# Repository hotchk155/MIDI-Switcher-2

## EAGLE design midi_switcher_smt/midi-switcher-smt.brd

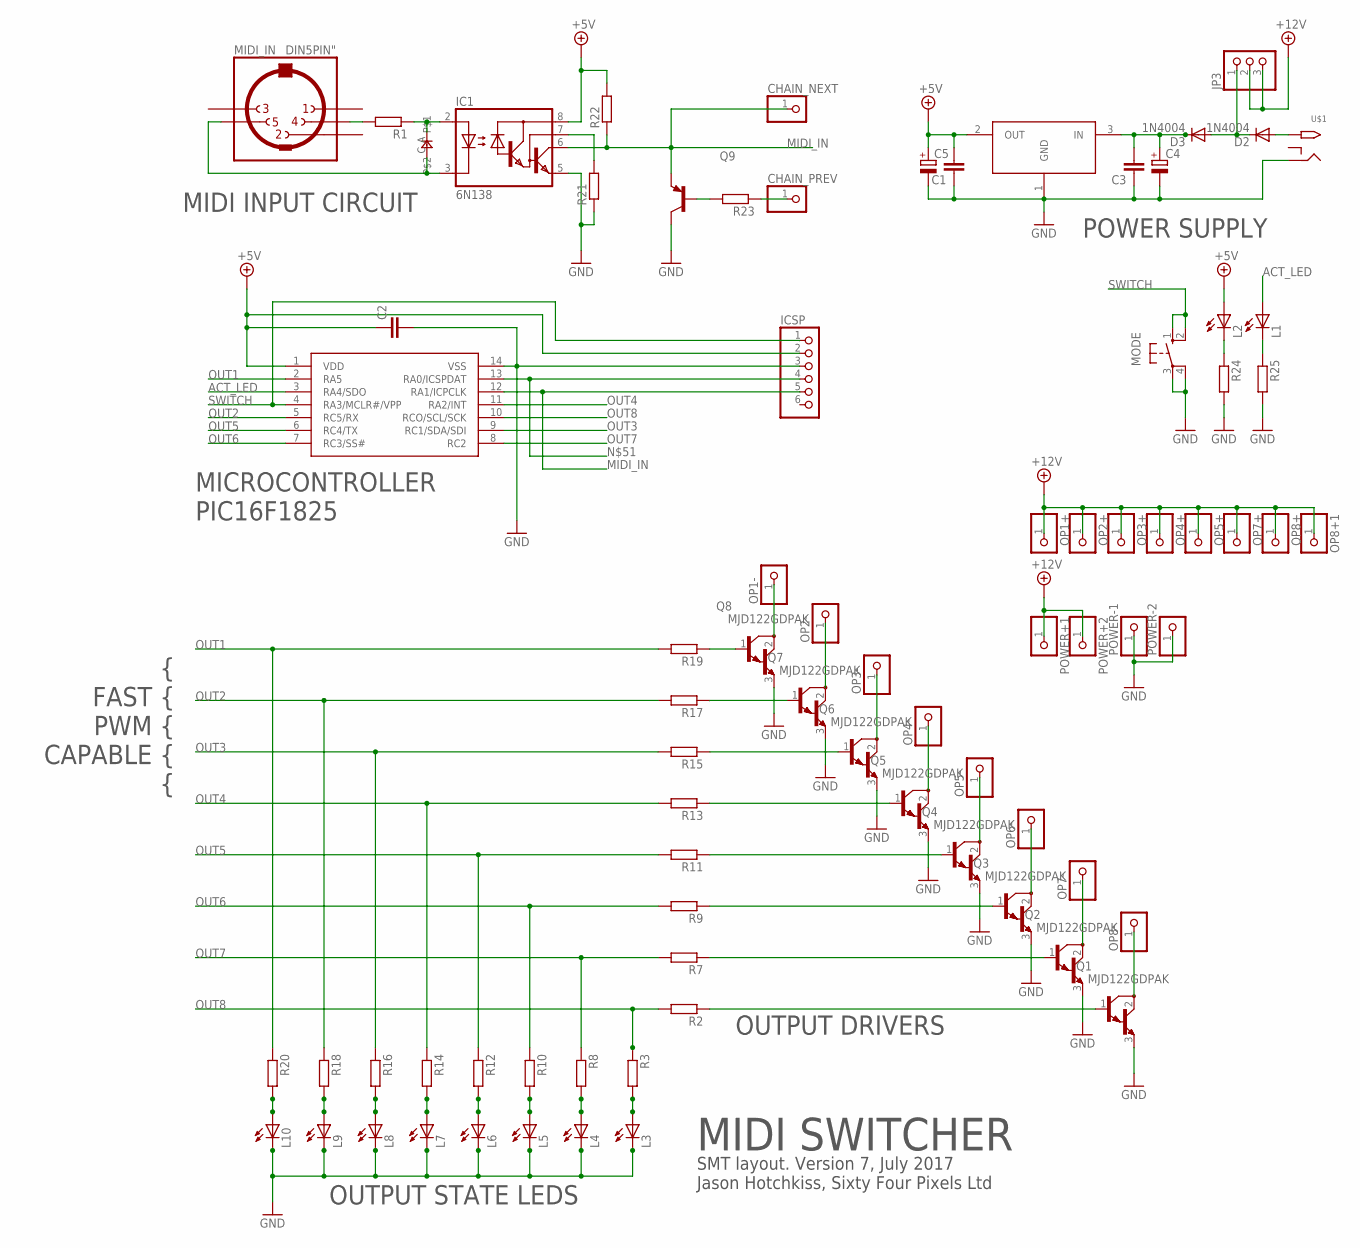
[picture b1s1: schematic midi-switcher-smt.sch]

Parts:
C1, C2, C3: C-EUC0805; C0805
C4: CPOL-EUE2.5-7; E2,5-7
C5: CPOL-EUE2.5-6; E2,5-6
CHAIN_NEXT: PINHD-1X1; 1X01
CHAIN_PREV: PINHD-1X1; 1X01
D1: 0805DIODE
D2, D3: 1N4004; DO-VERT
IC1: 6N138; DIL08
IC2: PIC16F1825SO14; SO14
IC3: LD1086; DPACK
ICSP: HEADER-1X6; 1X06_OVAL
JP3: PINHD-1X3; 1X03
L1, L2, L3, L4, L5, L6, L7, L8, L9, L10: LEDCHIP-LED0805; CHIP-LED0805
MIDI_IN: DIN5PIN"; TRUCONN90
MODE: 10-XX; B3F-10XX
OP1+, OP1-, OP2+, OP2-, OP3+, OP3-, OP4+, OP4-, OP5+, OP5-, OP6-, OP7+, OP7-, OP8+, OP8+1, OP8-: PINHD-1X1; 1X01W
POWER+1, POWER+2: PINHD-1X1; 1X01W
POWER-1, POWER-2: PINHD-1X1; 1X01W
Q1, Q2, Q3, Q4, Q5, Q6, Q7, Q8: MJD122GDPAK; DPACK
Q9: MMBT3906LT1-PNP-SOT23-BEC; SOT23-BEC
R1, R2, R3, R7, R8, R9, R10, R11, R12, R13, R14, R15, R16, R17, R18, R19, R20, R21, R22, R23, R24, R25: R-EU_R0805; R0805
U$1: 2.1MMJACKTHM; PJ-102A

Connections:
+5V: C1.2, C2.1, C5.+, IC1.8 (VCC), IC2.1 (VDD), IC3.2 (OUT), ICSP.2, L2.A, R22.2
+12V: JP3.2, JP3.3, OP1+.1, OP2+.1, OP3+.1, OP4+.1, OP5+.1, OP7+.1, OP8+.1, OP8+1.1, POWER+1.1, POWER+2.1
ACT_LED: IC2.3 (RA4/SDO), L1.A
GND: C1.1, C2.2, C3.1, C4.-, C5.-, IC1.5 (GND), IC2.14 (VSS), IC3.1 (GND), ICSP.3, L3.C, L4.C, L5.C, L6.C, L7.C, L8.C, L9.C, L10.C, MODE.3, MODE.4 (P1), POWER-1.1, POWER-2.1, Q1.3 (E), Q2.3 (E), Q3.3 (E), Q4.3 (E), Q5.3 (E), Q6.3 (E), Q7.3 (E), Q8.3 (E), Q9.C, R21.1, R24.2, R25.2, U$1.RING
MIDI_IN: CHAIN_NEXT.1, IC1.6 (VO), IC2.12 (RA1/ICPCLK), ICSP.5, Q9.E, R22.1
unnamed: D1.C, IC1.3 (C), MIDI_IN.5
unnamed: MIDI_IN.4, R1.2
unnamed: D1.A, IC1.2 (A), R1.1
unnamed: IC1.7 (VB), R21.2
unnamed: L1.C, R25.1
unnamed: L10.A, R20.2
unnamed: L9.A, R18.2
unnamed: Q8.1 (B), R19.1
unnamed: Q7.1 (B), R17.1
unnamed: Q6.1 (B), R15.1
unnamed: Q5.1 (B), R13.1
unnamed: Q4.1 (B), R11.1
unnamed: Q3.1 (B), R9.1
unnamed: Q2.1 (B), R7.1
unnamed: Q1.1 (B), R2.1
unnamed: Q9.B, R23.2
unnamed: CHAIN_PREV.1, R23.1
unnamed: L8.A, R16.2
unnamed: OP1-.1, Q8.2 (C)
unnamed: OP2-.1, Q7.2 (C)
unnamed: OP3-.1, Q6.2 (C)
unnamed: L2.C, R24.1
unnamed: OP5-.1, Q4.2 (C)
unnamed: OP6-.1, Q3.2 (C)
unnamed: OP4-.1, Q5.2 (C)
unnamed: L7.A, R14.2
unnamed: L6.A, R12.2
unnamed: L5.A, R10.2
unnamed: L4.A, R8.2
unnamed: L3.A, R3.2
unnamed: C3.2, C4.+, D3.C, IC3.3 (IN)
unnamed: OP7-.1, Q2.2 (C)
unnamed: D2.A, U$1.TIP
unnamed: OP8-.1, Q1.2 (C)
unnamed: IC2.13 (RA0/ICSPDAT), ICSP.4
unnamed: D2.C, D3.A, JP3.1
OUT1: IC2.2 (RA5), R19.2, R20.1
OUT2: IC2.5 (RC5/RX), R17.2, R18.1
OUT3: IC2.9 (RC1/SDA/SDI), R15.2, R16.1
OUT4: IC2.11 (RA2/INT), R13.2, R14.1
OUT5: IC2.6 (RC4/TX), R11.2, R12.1
OUT6: IC2.7 (RC3/SS#), R9.2, R10.1
OUT7: IC2.8 (RC2), R7.2, R8.1
OUT8: IC2.10 (RCO/SCL/SCK), R2.2, R3.1
SWITCH: IC2.4 (RA3/MCLR#/VPP), ICSP.1, MODE.1 (S), MODE.2 (S1)

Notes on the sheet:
MIDI SWITCHER
SMT layout. Version 7, July 2017 Jason Hotchkiss, Sixty Four Pixels Ltd
MIDI INPUT CIRCUIT
MICROCONTROLLER PIC16F1825
POWER SUPPLY
OUTPUT STATE LEDS
OUTPUT DRIVERS
{ FAST { PWM { CAPABLE { {

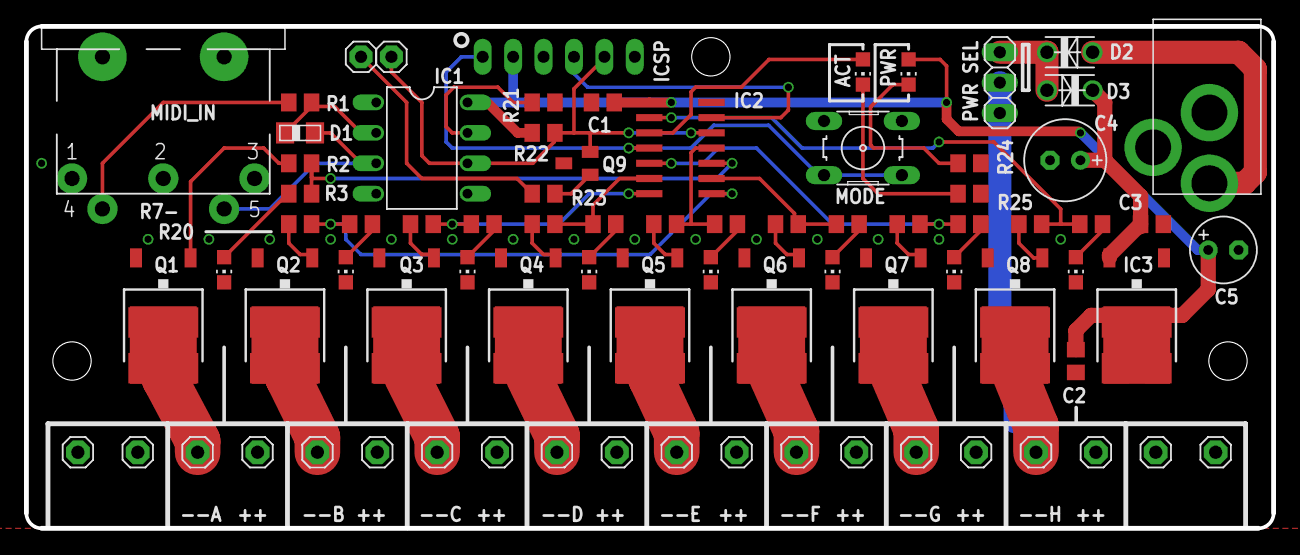
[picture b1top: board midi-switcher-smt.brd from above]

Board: 2 copper layers, 104.1 x 41.9 mm, 79 parts (0 on the bottom side), 50 nets.

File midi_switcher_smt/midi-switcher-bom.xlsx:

Comment | Designator | Footprint | JLCPCB Part #（optional）
100n | C1 | 0805
100n | C2 | 0805
100n | C3 | 0805
TS4148 | D1 | 0805
PIC16F1825-I/SL | IC2 | SOIC-14 | C19649
LD1086DT50TR | IC3 | DPAK | C164853
blue | L1 | 0805
red | L2 | 0805
blue | L3 | 0805
blue | L4 | 0805
blue | L5 | 0805
blue | L6 | 0805
blue | L7 | 0805
blue | L8 | 0805
blue | L9 | 0805
blue | L10 | 0805
MJD122G | Q1 | DPAK | C89910
MJD122G | Q2 | DPAK | C89910
MJD122G | Q3 | DPAK | C89910
MJD122G | Q4 | DPAK | C89910
MJD122G | Q5 | DPAK | C89910
MJD122G | Q6 | DPAK | C89910
MJD122G | Q7 | DPAK | C89910
MJD122G | Q8 | DPAK | C89910
MMBT3906 | Q9 | SOT23-3
220 | R1 | R0805
1k | R2 | R0805
1k | R3 | R0805
1k | R7 | R0805
1k | R8 | R0805
1k | R9 | R0805
1k | R10 | R0805
1k | R11 | R0805
1k | R12 | R0805
1k | R13 | R0805
1k | R14 | R0805
1k | R15 | R0805
1k | R16 | R0805
1k | R17 | R0805
1k | R18 | R0805
1k | R19 | R0805
1k | R20 | R0805
1.5k | R21 | R0805
1.5k | R22 | R0805
1k | R23 | R0805
1k | R24 | R0805
1k | R25 | R0805

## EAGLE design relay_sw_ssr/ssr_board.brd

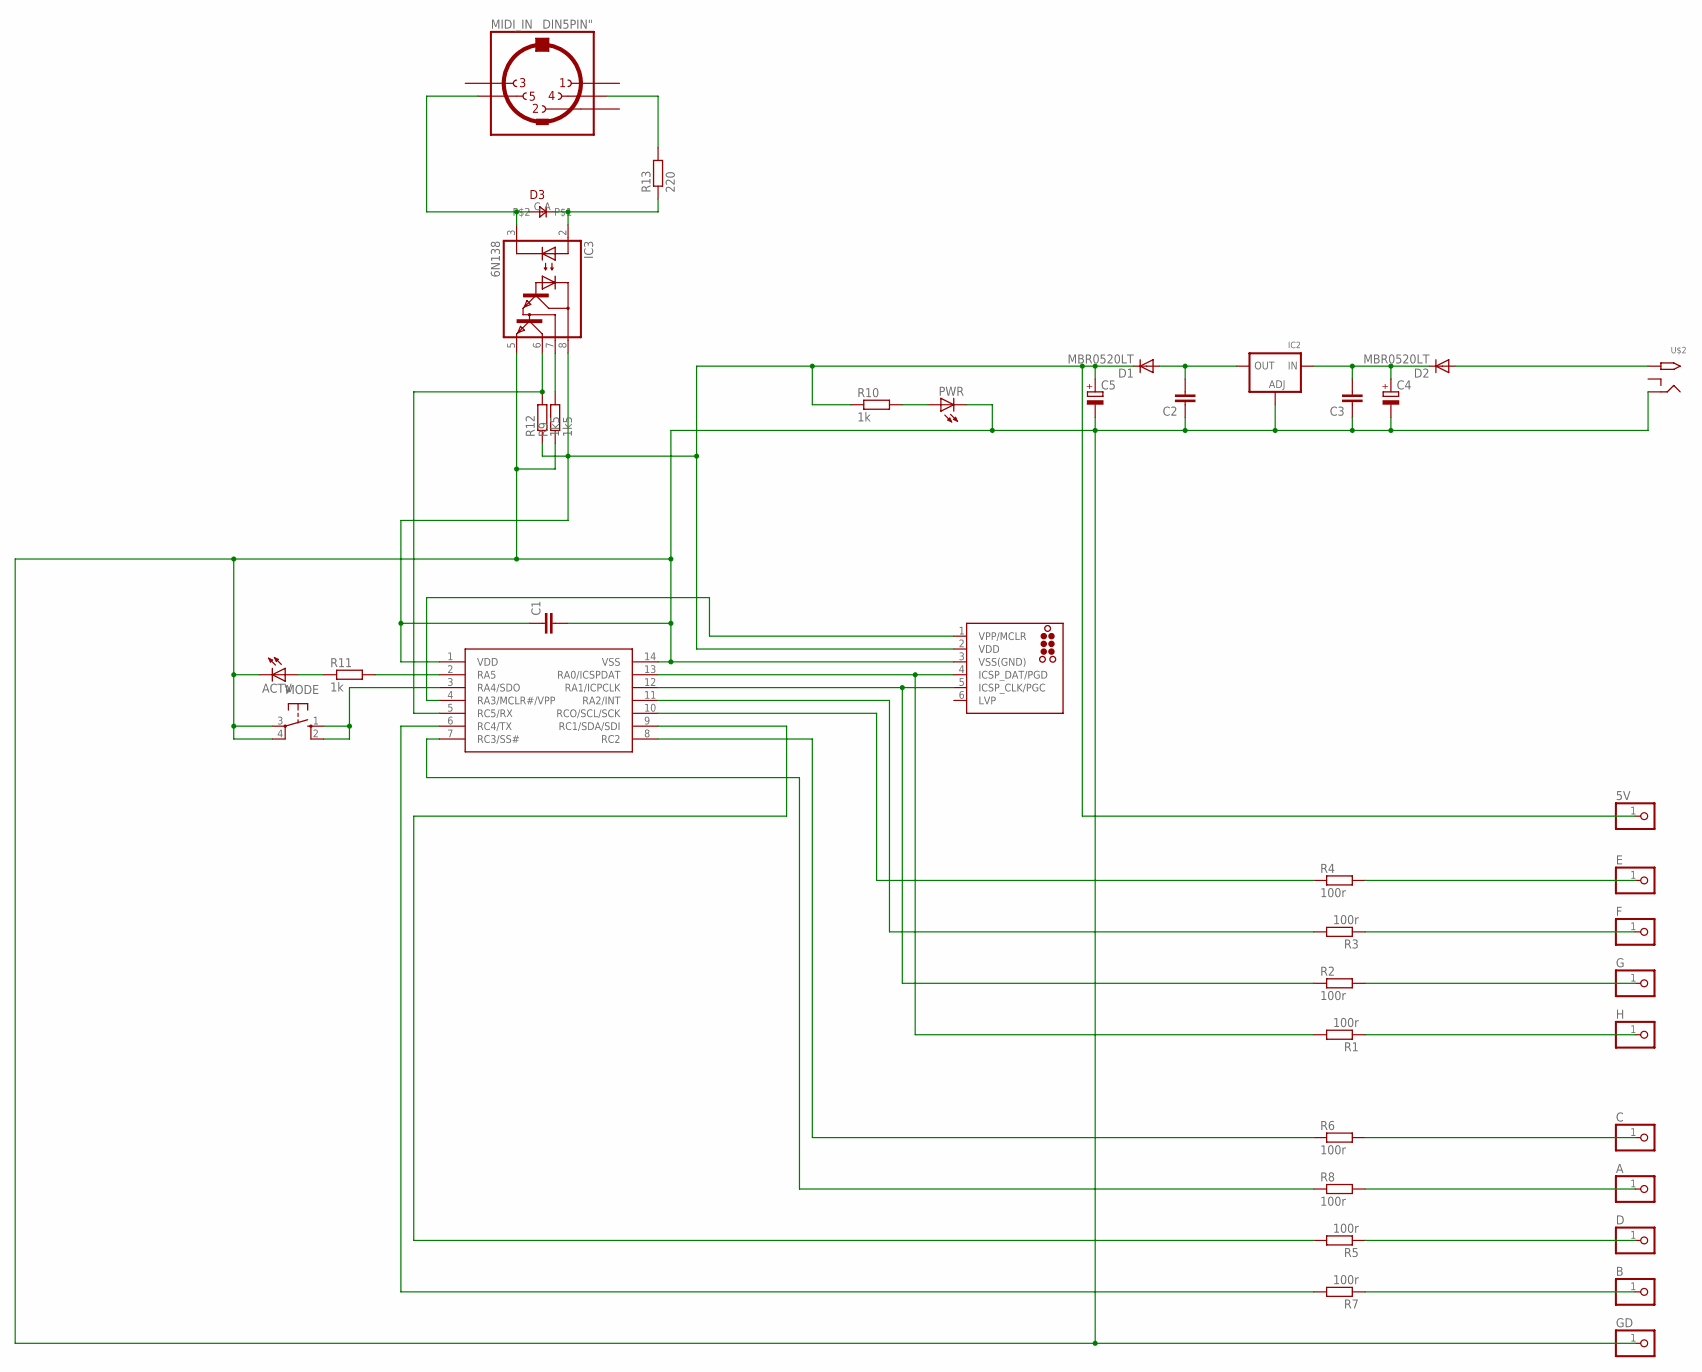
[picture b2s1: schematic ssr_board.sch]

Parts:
5V: PINHD-1X1; 1X01
A: PINHD-1X1; 1X01
ACTV: LED3MM
B: PINHD-1X1; 1X01
C: PINHD-1X1; 1X01
C1, C2, C3: C-EUC0805; C0805
C4, C5: CPOL-EUE2-5; E2-5
D: PINHD-1X1; 1X01
D1, D2: MBR0520LT; SOD123
D3: 0805DIODE
E: PINHD-1X1; 1X01
F: PINHD-1X1; 1X01
G: PINHD-1X1; 1X01
GD: PINHD-1X1; 1X01
H: PINHD-1X1; 1X01
IC1: PIC16F1825SO14; SO14
IC2: LM1117SOT223-WAVE; SOT223-W
IC3: 6N138; DIL08
ICSP: TC2030-MCP-NL
MIDI_IN: DIN5PIN"; TRUCONN90
MODE: 10-XX; B3F-10XX
PWR: LED3MM
R1, R2, R3, R4, R5, R6, R7, R8: 100r; R0805
R9, R12: 1k5; R0805
R10, R11: 1k; R0805
R13: 220; R0805
U$2: 2.1MMJACKTHM; PJ-102A

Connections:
5V: 5V.1, C1.1, C5.+, D1.C, IC1.1 (VDD), IC3.8 (VCC), ICSP.2 (VDD), R10.1, R12.1
GND: ACTV.K (C), C1.2, C2.1, C3.1, C4.-, C5.-, GD.1, IC1.14 (VSS), IC2.1 (ADJ), IC3.5 (GND), ICSP.3 (VSS(GND)), MODE.3, MODE.4 (P1), PWR.K (C), R9.1, U$2.RING
unnamed: C2.2, D1.A, IC2.2 (OUT)
unnamed: D2.A, U$2.TIP
unnamed: PWR.A, R10.2
unnamed: C3.2, C4.+, D2.C, IC2.3 (IN)
unnamed: MIDI_IN.4, R13.2
unnamed: D3.A, IC3.2 (A), R13.1
unnamed: D3.C, IC3.3 (C), MIDI_IN.5
unnamed: IC3.7 (VB), R9.2
unnamed: F.1, R3.1
unnamed: G.1, R2.2
unnamed: H.1, R1.1
unnamed: C.1, R6.2
unnamed: A.1, R8.2
unnamed: D.1, R5.1
unnamed: B.1, R7.1
unnamed: IC1.12 (RA1/ICPCLK), ICSP.5 (ICSP_CLK/PGC), R2.1
unnamed: IC1.13 (RA0/ICSPDAT), ICSP.4 (ICSP_DAT/PGD), R1.2
unnamed: IC1.8 (RC2), R6.1
unnamed: IC1.7 (RC3/SS#), R8.1
unnamed: IC1.9 (RC1/SDA/SDI), R5.2
unnamed: IC1.6 (RC4/TX), R7.2
unnamed: E.1, R4.2
unnamed: IC1.4 (RA3/MCLR#/VPP), ICSP.1 (VPP/MCLR)
unnamed: IC1.3 (RA4/SDO), MODE.1 (S), MODE.2 (S1)
unnamed: IC1.11 (RA2/INT), R3.2
unnamed: IC1.10 (RCO/SCL/SCK), R4.1
unnamed: IC1.5 (RC5/RX), IC3.6 (VO), R12.2
unnamed: ACTV.A, R11.1
unnamed: IC1.2 (RA5), R11.2

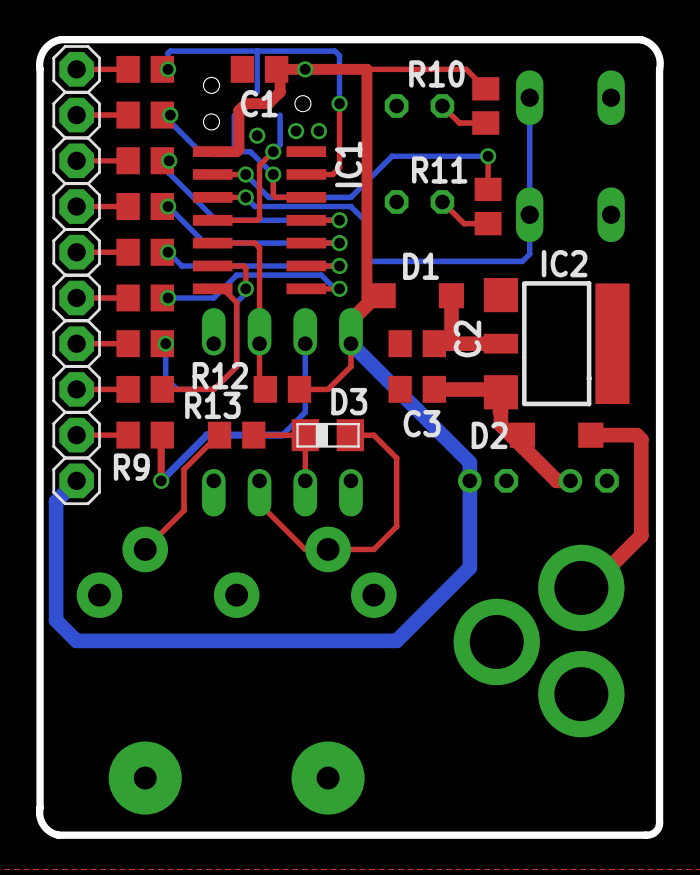
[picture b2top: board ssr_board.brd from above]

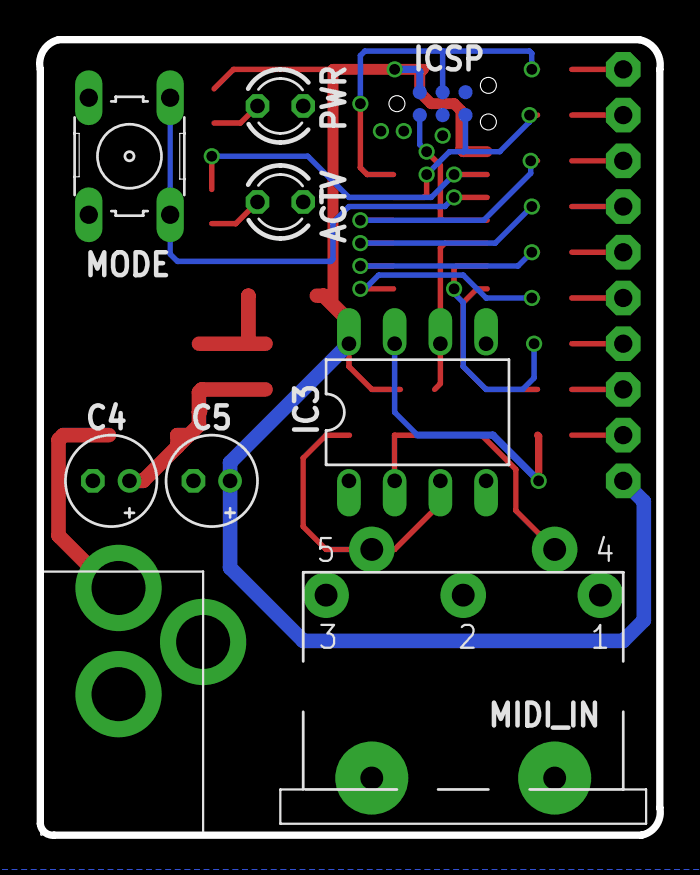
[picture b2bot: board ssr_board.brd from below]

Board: 2 copper layers, 34.5 x 44.2 mm, 40 parts (9 on the bottom side), 31 nets.

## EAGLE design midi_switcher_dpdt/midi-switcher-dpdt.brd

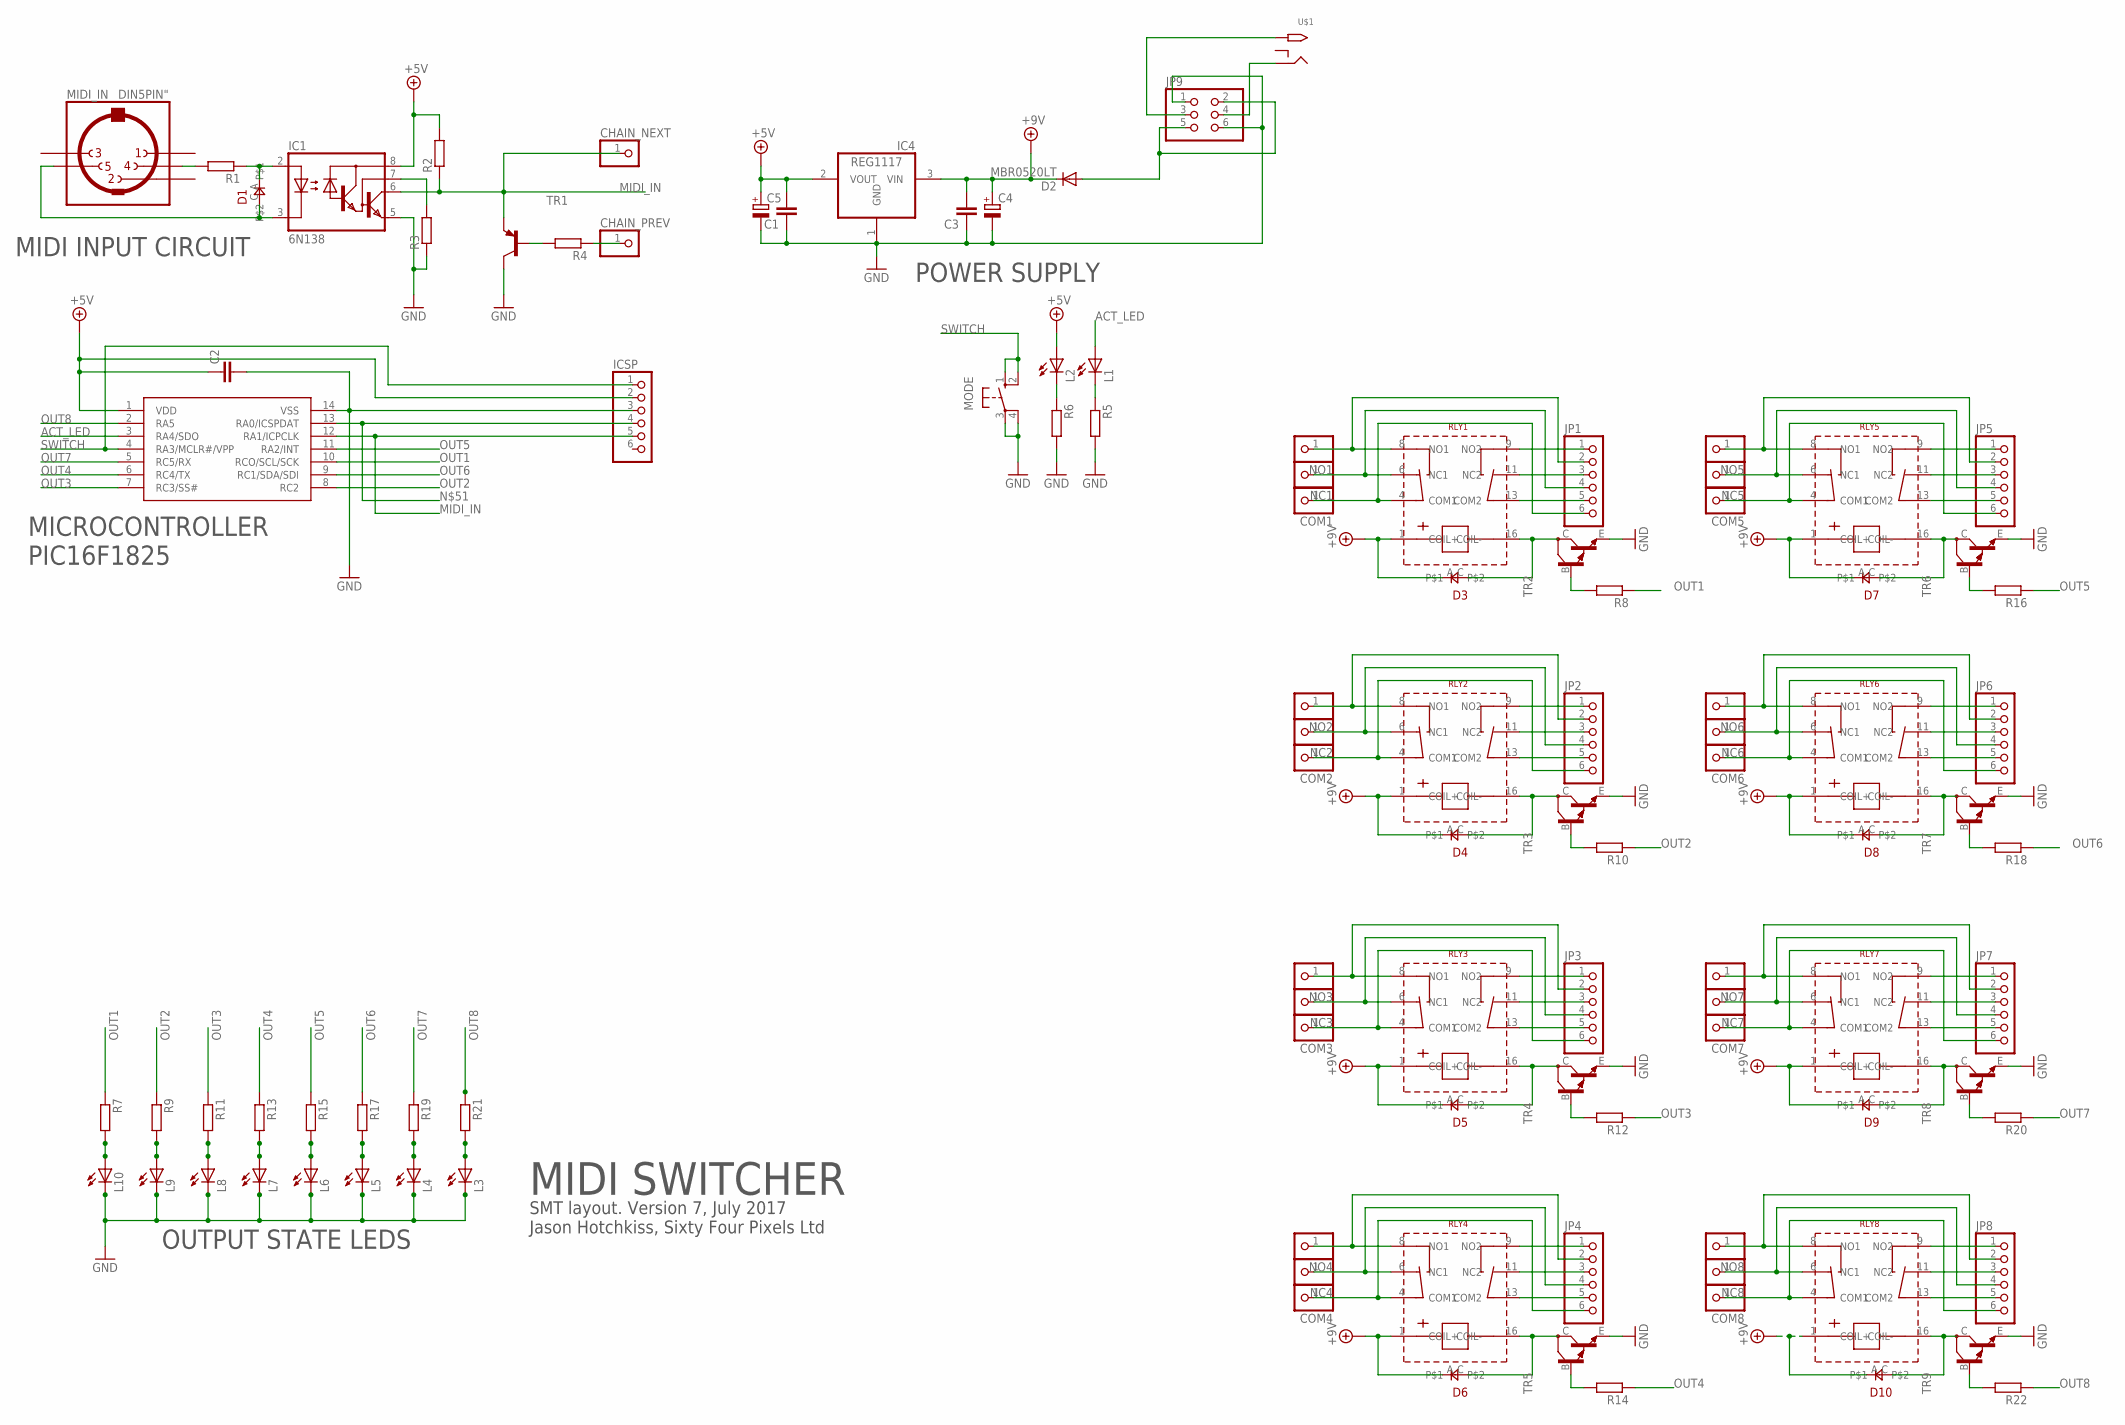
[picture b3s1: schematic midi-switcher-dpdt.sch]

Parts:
C1, C2, C3: C-EUC0805; C0805
C4, C5: CPOL-EUE2,5-6E; E2,5-6E
CHAIN_NEXT: PINHD-1X1; 1X01
CHAIN_PREV: PINHD-1X1; 1X01
COM1, COM2, COM3, COM4, COM5, COM6, COM7, COM8: PINHD-1X1; 1X01
D1, D3, D4, D5, D6, D7, D8, D9, D10: 0805DIODE
D2: MBR0520LT; SOD123
IC1: 6N138; DIL08
IC2: PIC16F1825SO14; SO14
IC4: REG1117; SOT223
ICSP: HEADER-1X6; 1X06_OVAL
JP1, JP2, JP3, JP4, JP5, JP6, JP7, JP8: PINHD-1X6; 1X06
JP9: PINHD-2X3; 2X03
L1, L2, L3, L4, L5, L6, L7, L8, L9, L10: LEDCHIP-LED0805; CHIP-LED0805
MIDI_IN: DIN5PIN"; TRUCONN90
MODE: 10-XX; B3F-10XX
NC1, NC2, NC3, NC4, NC5, NC6, NC7, NC8: PINHD-1X1; 1X01
NO1, NO2, NO3, NO4, NO5, NO6, NO7, NO8: PINHD-1X1; 1X01
R1, R2, R3, R4, R5, R6, R7, R8, R9, R10, R11, R12, R13, R14, R15, R16, R17, R18, R19, R20, R21, R22: R-EU_R0805; R0805
RLY1, RLY2, RLY3, RLY4, RLY5, RLY6, RLY7, RLY8: HFD2RELAY
TR1: MMBT3906LT1-PNP-SOT23-BEC; SOT23-BEC
TR2, TR3, TR4, TR5, TR6, TR7, TR8, TR9: MMBTA13LT1-NPN_DARL-SOT23-BEC; SOT23-BEC
U$1: 2.1MMJACKTHM; PJ-102A

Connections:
+5V: C1.2, C2.1, C5.+, IC1.8 (VCC), IC2.1 (VDD), IC4.2 (VOUT), ICSP.2, L2.A, R2.2
+9V: C3.2, C4.+, D2.C, D3.A, D4.A, D5.A, D6.A, D7.A, D8.A, D9.A, D10.A, IC4.3 (VIN), RLY1.1 (COIL+), RLY2.1 (COIL+), RLY3.1 (COIL+), RLY4.1 (COIL+), RLY5.1 (COIL+), RLY6.1 (COIL+), RLY7.1 (COIL+), RLY8.1 (COIL+)
ACT_LED: IC2.3 (RA4/SDO), L1.A
GND: C1.1, C2.2, C3.1, C4.-, C5.-, IC1.5 (GND), IC2.14 (VSS), IC4.1 (GND), ICSP.3, JP9.1, JP9.6, L3.C, L4.C, L5.C, L6.C, L7.C, L8.C, L9.C, L10.C, MODE.3, MODE.4 (P1), R3.1, R5.2, R6.2, TR1.C, TR2.E, TR3.E, TR4.E, TR5.E, TR6.E, TR7.E, TR8.E, TR9.E
MIDI_IN: CHAIN_NEXT.1, IC1.6 (VO), IC2.12 (RA1/ICPCLK), ICSP.5, R2.1, TR1.E
unnamed: D1.C, IC1.3 (C), MIDI_IN.5
unnamed: MIDI_IN.4, R1.2
unnamed: D1.A, IC1.2 (A), R1.1
unnamed: IC1.7 (VB), R3.2
unnamed: L1.C, R5.1
unnamed: L10.A, R7.2
unnamed: L9.A, R9.2
unnamed: D3.C, RLY1.16 (COIL-), TR2.C
unnamed: R8.2, TR2.B
unnamed: JP9.3, U$1.TIP
unnamed: D4.C, RLY2.16 (COIL-), TR3.C
unnamed: R10.2, TR3.B
unnamed: JP9.4, U$1.RING
unnamed: D5.C, RLY3.16 (COIL-), TR4.C
unnamed: R12.2, TR4.B
unnamed: R4.2, TR1.B
unnamed: CHAIN_PREV.1, R4.1
unnamed: D6.C, RLY4.16 (COIL-), TR5.C
unnamed: R14.2, TR5.B
unnamed: D2.A, JP9.2, JP9.5
unnamed: JP1.2, NO1.1, RLY1.8 (NO1)
unnamed: L8.A, R11.2
unnamed: JP1.4, NC1.1, RLY1.6 (NC1)
unnamed: JP5.5, RLY5.13 (COM2)
unnamed: JP2.2, NO2.1, RLY2.8 (NO1)
unnamed: L2.C, R6.1
unnamed: JP2.4, NC2.1, RLY2.6 (NC1)
unnamed: COM2.1, JP2.6, RLY2.4 (COM1)
unnamed: JP3.2, NO3.1, RLY3.8 (NO1)
unnamed: JP3.4, NC3.1, RLY3.6 (NC1)
unnamed: L7.A, R13.2
unnamed: COM3.1, JP3.6, RLY3.4 (COM1)
unnamed: L6.A, R15.2
unnamed: L5.A, R17.2
unnamed: L4.A, R19.2
unnamed: L3.A, R21.2
unnamed: JP4.2, NO4.1, RLY4.8 (NO1)
unnamed: JP4.4, NC4.1, RLY4.6 (NC1)
unnamed: COM4.1, JP4.6, RLY4.4 (COM1)
unnamed: JP5.2, NO5.1, RLY5.8 (NO1)
unnamed: JP5.4, NC5.1, RLY5.6 (NC1)
unnamed: COM5.1, JP5.6, RLY5.4 (COM1)
unnamed: JP6.2, NO6.1, RLY6.8 (NO1)
unnamed: JP6.4, NC6.1, RLY6.6 (NC1)
unnamed: COM6.1, JP6.6, RLY6.4 (COM1)
unnamed: JP7.2, NO7.1, RLY7.8 (NO1)
unnamed: JP7.4, NC7.1, RLY7.6 (NC1)
unnamed: COM7.1, JP7.6, RLY7.4 (COM1)
unnamed: IC2.13 (RA0/ICSPDAT), ICSP.4
unnamed: JP8.2, NO8.1, RLY8.8 (NO1)
unnamed: JP8.4, NC8.1, RLY8.6 (NC1)
unnamed: COM8.1, JP8.6, RLY8.4 (COM1)
unnamed: D7.C, RLY5.16 (COIL-), TR6.C
unnamed: R16.2, TR6.B
unnamed: D8.C, RLY6.16 (COIL-), TR7.C
unnamed: R18.2, TR7.B
unnamed: D9.C, RLY7.16 (COIL-), TR8.C
unnamed: R20.2, TR8.B
unnamed: D10.C, RLY8.16 (COIL-), TR9.C
unnamed: R22.2, TR9.B
unnamed: JP5.3, RLY5.11 (NC2)
unnamed: JP1.5, RLY1.13 (COM2)
unnamed: JP1.3, RLY1.11 (NC2)
unnamed: JP1.1, RLY1.9 (NO2)
unnamed: JP5.1, RLY5.9 (NO2)
unnamed: COM1.1, JP1.6, RLY1.4 (COM1)
unnamed: JP2.1, RLY2.9 (NO2)
unnamed: JP2.3, RLY2.11 (NC2)
unnamed: JP2.5, RLY2.13 (COM2)
unnamed: JP3.5, RLY3.13 (COM2)
unnamed: JP3.1, RLY3.9 (NO2)
unnamed: JP3.3, RLY3.11 (NC2)
unnamed: JP4.5, RLY4.13 (COM2)
unnamed: JP4.3, RLY4.11 (NC2)
unnamed: JP4.1, RLY4.9 (NO2)
unnamed: JP6.5, RLY6.13 (COM2)
unnamed: JP6.3, RLY6.11 (NC2)
unnamed: JP6.1, RLY6.9 (NO2)
unnamed: JP7.5, RLY7.13 (COM2)
unnamed: JP7.3, RLY7.11 (NC2)
unnamed: JP7.1, RLY7.9 (NO2)
unnamed: JP8.5, RLY8.13 (COM2)
unnamed: JP8.3, RLY8.11 (NC2)
unnamed: JP8.1, RLY8.9 (NO2)
OUT1: IC2.10 (RCO/SCL/SCK), R7.1, R8.1
OUT2: IC2.8 (RC2), R9.1, R10.1
OUT3: IC2.7 (RC3/SS#), R11.1, R12.1
OUT4: IC2.6 (RC4/TX), R13.1, R14.1
OUT5: IC2.11 (RA2/INT), R15.1, R16.1
OUT6: IC2.9 (RC1/SDA/SDI), R17.1, R18.1
OUT7: IC2.5 (RC5/RX), R19.1, R20.1
OUT8: IC2.2 (RA5), R21.1, R22.1
SWITCH: IC2.4 (RA3/MCLR#/VPP), ICSP.1, MODE.1 (S), MODE.2 (S1)

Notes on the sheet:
MIDI SWITCHER
SMT layout. Version 7, July 2017 Jason Hotchkiss, Sixty Four Pixels Ltd
MIDI INPUT CIRCUIT
MICROCONTROLLER PIC16F1825
POWER SUPPLY
OUTPUT STATE LEDS

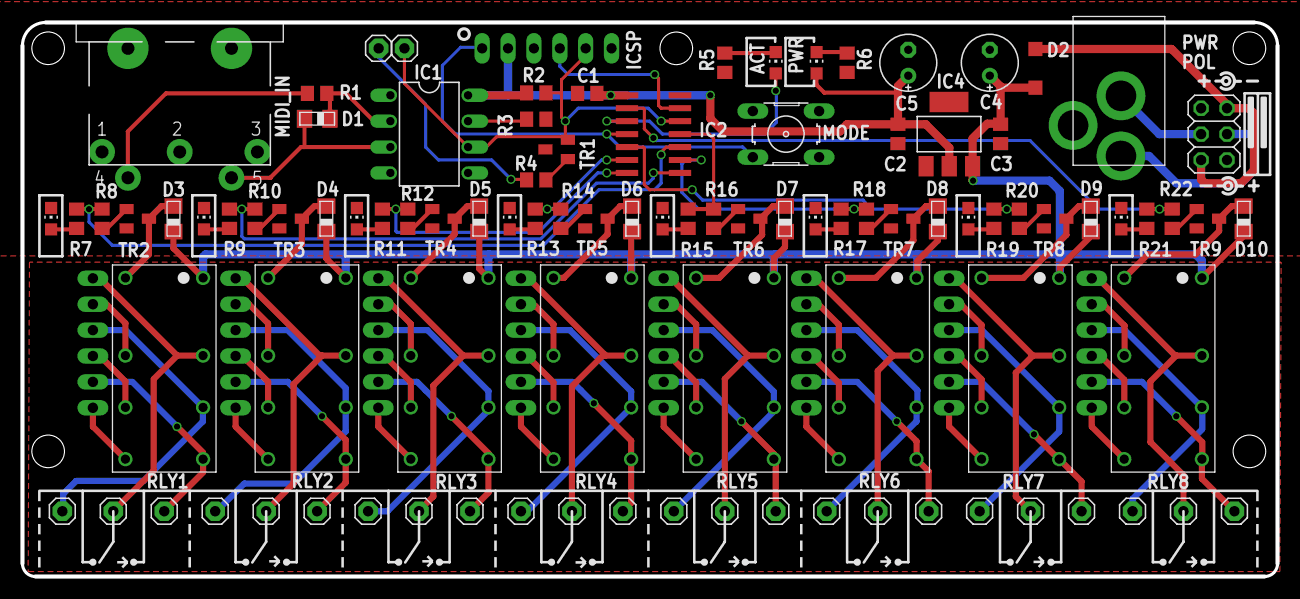
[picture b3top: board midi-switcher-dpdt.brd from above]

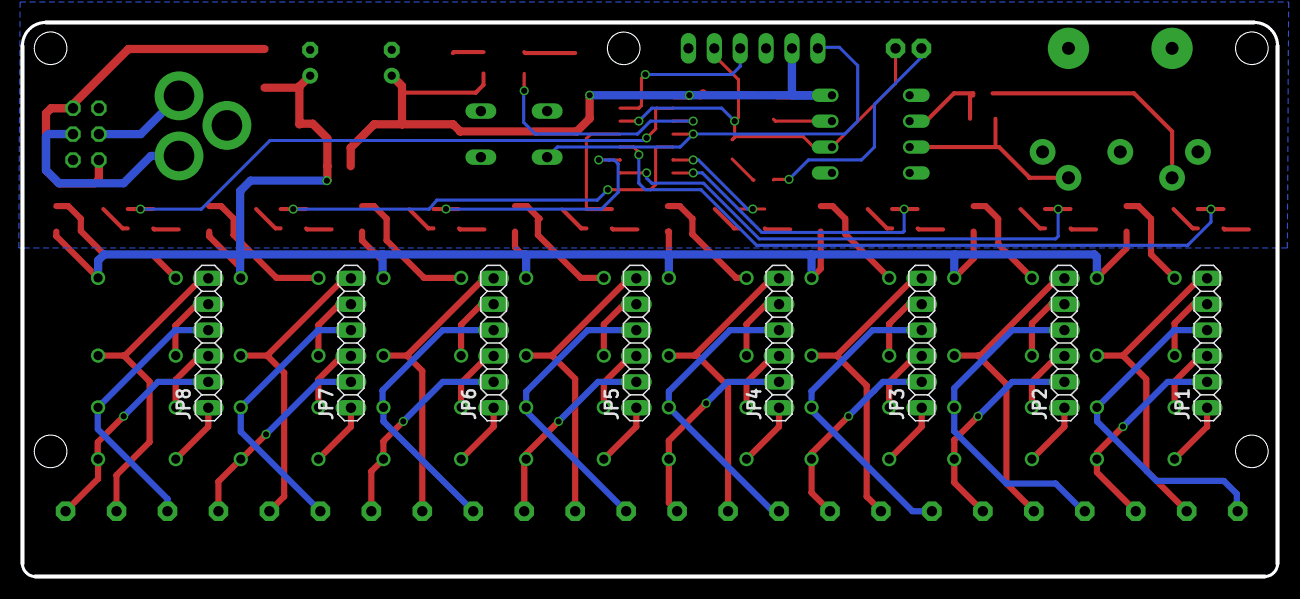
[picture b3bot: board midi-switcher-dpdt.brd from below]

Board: 2 copper layers, 123.1 x 54.4 mm, 106 parts (8 on the bottom side), 98 nets.

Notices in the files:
midi_switcher_smt/midi-switcher-smt.brd:
creativecommons.org/licenses
parts and their libraries:
tag-connect: ©2009 ROFA.cz - modified and updated by Robert Darlington ‹rdarlington@gmail.com›
